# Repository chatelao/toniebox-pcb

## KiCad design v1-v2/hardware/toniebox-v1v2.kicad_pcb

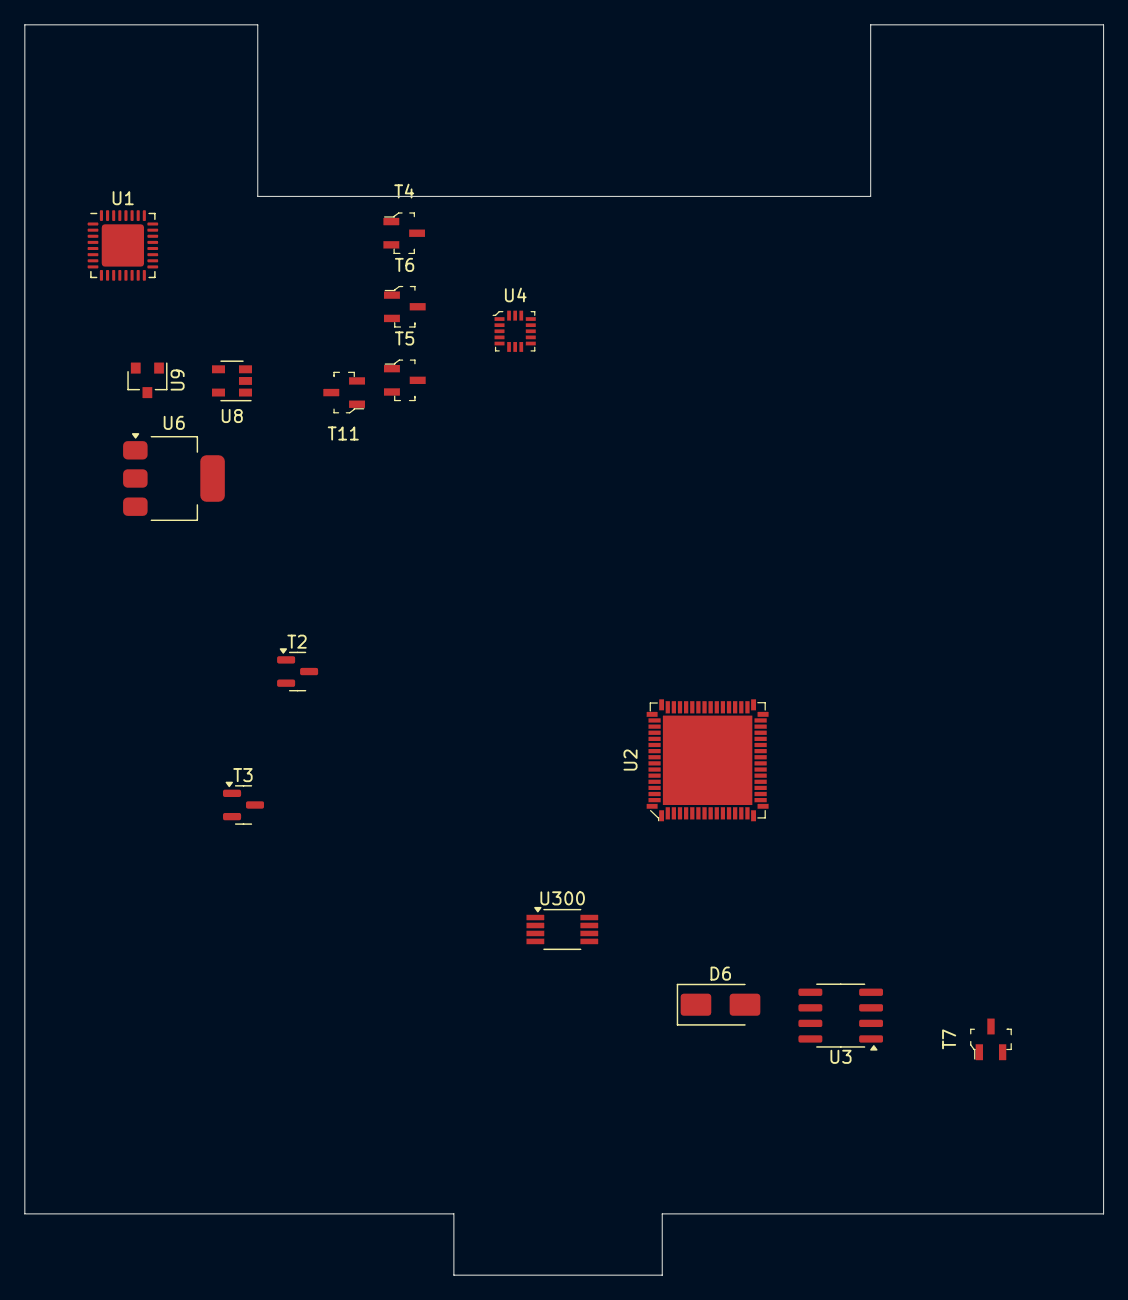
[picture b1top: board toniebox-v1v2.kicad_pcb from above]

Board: 2 copper layers, 88.0 x 102.0 mm, 16 parts (0 on the bottom side), 10 nets, no tracks yet.

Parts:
D6: SS14; D_SMA
T2, T3: MMBT3904; SOT-23
T4, T5, T6, T7, T11: FDV301N; SOT-23-3
U1: TLV320DAC3100; Texas_S-PVQFN-N32_EP3.45x3.45mm
U2: CC3200R1M2RGCR; VFQFN-64-1EP_9x9mm
U3: IS25LQ032B-JNLE; SOIC-8_3.9x4.9mm_P1.27mm
U4: MMA8451QT; VQFN-16_3x3mm
U6: AP2114H-3.3TRG1; SOT-223-3_TabPin2
U8: AP2112K-3.3; SOT-23-5
U9: AP2120N-1.8; SOT-23
U300: LM3485MM; VSSOP-8_3.0x3.0mm_P0.65mm

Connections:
+3V3: U2.10 (VIN_IO1), U6.2 (VO)
/I2C_SCL: U1.10 (SCL), U2.3 (GPIO12), U4.4 (SCL)
/I2C_SDA: U1.9 (SDA), U2.4 (GPIO13), U4.6 (SDA)
/TBC2: U3.3 (~WP/IO2), U3.7 (~HOLD/IO3)
/TBC3: U2.61 (GPIO6), U8.3 (EN)
GND: T4.2 (S), T5.2 (S), T7.2 (S), T11.2 (S), U1.1 (IOVSS), U4.7 (SA0)
unnamed: T7.1 (G), U2.21 (SOP2)
unnamed: T7.3 (D), U2.35 (SOP0)
unnamed: T6.2 (S), T11.3 (D)
VDD: T11.1 (G), U1.2 (IOVDD), U4.1 (VDDIO), U8.5 (VOUT)

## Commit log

2024-05-07 Chg - KiCAD upgrade, More components
